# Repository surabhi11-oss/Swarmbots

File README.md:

# Swarmbots - Autonomous Robotic Swarm Platform

Autonomous multi-robot swarm platform featuring distributed mesh coordination, differential-drive motion control, an onboard OLED graphical interface, and a zero-install real-time Web Digital Twin.

---

## Repository Structure

```
Swarmbots/
├── firmware/
│   ├── main/                          # Core autonomous robot firmware & motor drivers
│   │   ├── SwarmBot/                  # Main ESP32 sketch for full swarm operations
│   │   └── README.md
│   ├── oled/                          # Unified OLED Display & Web Subsystem
│   │   ├── SwarmBot_OLED/             # Standalone production ESP32 OLED firmware
│   │   │   ├── SwarmBot_OLED.ino      # Main sketch entry point & cooperative scheduler
│   │   │   ├── config.h               # Global compile-time defaults & pin mappings
│   │   │   └── src/
│   │   │       ├── config/            # Non-Volatile Storage (NVS) & pin validation
│   │   │       ├── controllers/       # Motor safety & autonomous pause hooks
│   │   │       ├── display/           # U8g2 abstraction & runtime I2C scanner
│   │   │       ├── input/             # Single-button multi-gesture state machine
│   │   │       ├── state/             # Centralized robot telemetry & UI state model
│   │   │       ├── ui/                # UI rendering, boot animation & XBM assets
│   │   │       └── web/               # SoftAP Web server, live digital twin & API
│   │   ├── swarmbot_simulator.html    # Standalone browser testing & interaction harness
│   │   └── README.md                  # Comprehensive OLED subsystem documentation
│   ├── display/                       # Display drivers and documentation
│   └── tests/                         # Hardware diagnostic scripts & sensor tests
└── README.md                          # Repository master documentation
```

---

## OLED & Human-Machine Interface (HMI) Subsystem

The OLED subsystem located at [`firmware/oled/SwarmBot_OLED/`](firmware/oled/SwarmBot_OLED/) provides an interactive interface for configuring, monitoring, and debugging swarm robots without requiring a physical serial connection.

### 1. Key Features
- **Official "Hexa Swarm + S" Logo Boot Animation**:
  - Procedural 7-stage boot sequence rendering 6 swarm nodes, hexagon edges, a 3-pixel thick stylized "S" mark, and a typewriter reveal of `SWARM BOT`.
- **Single-Button Multi-Gesture Finite State Machine**:
  - Designed for minimal hardware complexity using a single tactile switch on `GPIO 27`:
    - **Single Tap (< 450 ms)**: Cycle forward / Next option.
    - **Double Tap (< 350 ms)**: Back / Exit submenu.
    - **Select Hold (1.2 s – 2.8 s)**: Confirm / Enter selected utility.
    - **Power Hold (≥ 3.0 s on Home)**: Emergency Power Halt / Confirmation screen.
- **Smartwatch-Style Carousel Menu**:
  - Smooth 5-item horizontal carousel featuring monochrome XBM icons: `MODES`, `SETTINGS`, `CREDITS`, `POWER`, and `RETURN`.
- **Comprehensive Screen Hierarchy**:
  - `Boot Screen`: Procedural logo reveal and initialization.
  - `Home Screen`: Bot ID, live battery %, dynamic battery icon, textual peer connectivity (`4/4 CONNECTED`), and operational mode chip.
  - `Mode Select`: `Follow Leader` and `Manual Control`.
  - `Sub-Utilities`: Leader tracking distance, speed overrides, and manual drive telemetry.
  - `Settings`: Live I2C address, driver selection, GPIO mappings, and SoftAP IP.
  - `Credits`: Rolling department and team credits (`ECS DEPT - VESIT`).
  - `Power Confirmation & Safe Shutdown`: Hardware latch power-down sequence.
- **Safety Lock (Autonomous Motion Pause)**:
  - While navigating the menu system, autonomous motor actuation is paused automatically to prevent physical collision while handling the robot.

---

## Web Remote & Live 128×64 Digital Twin

The ESP32 broadcasts a self-hosted Wi-Fi Access Point (`SSID: SwarmBot-01`, default IP `192.168.4.1`):

- **Bi-Directional Digital Twin**: Renders a 1:1 pixel-perfect 128×64 HTML5 Canvas representation of the OLED display in real-time.
- **Tactile Button Simulation**:
  - Includes a real-time **60 FPS live hold timer** (`⏱️ 1450 ms`).
  - Smooth dynamic progress bar filling from 0 ms to 3000 ms.
  - Dynamic visual feedback: glowing emerald green ring at 1.5s (Select), pulsing crimson red ring at 3s (Power).
- **Quick Test Shortcuts**: Instant 1-click test chips for `Tap`, `Double-Tap`, `Hold 1.5s`, and `Hold 3s`.
- **Runtime I2C Bus Scanner**: Scan connected I2C peripherals directly from the web browser.
- **NVS Settings Editor**: Change Bot ID, pin assignments, and display driver without recompiling.

---

## Default Pin Mapping

| Peripheral | Signal | ESP32 GPIO | Description |
|---|---|---|---|
| **OLED Display** | SDA | `GPIO 21` | I2C Data Line (SH1106 / SSD1306) |
| **OLED Display** | SCL | `GPIO 22` | I2C Clock Line (400 kHz Fast Mode) |
| **Tactile Button** | SW | `GPIO 27` | Active-LOW pushbutton with internal pull-up |
| **Battery ADC** | V_BAT | `GPIO 34` | ADC1 analog input (resistor divider) |
| **Left Motor** | PWM / DIR | `GPIO 18 / 19` | Differential drive left channel |
| **Right Motor** | PWM / DIR | `GPIO 23 / 5` | Differential drive right channel |
| **Power Latch** | EN | `GPIO -1` (Opt) | Optional auto-power-off latch |

> **Safe Recovery Mode:** If an invalid GPIO configuration is saved to NVS, hold `GPIO 27` down for 5 seconds during power-up to restore all factory defaults.

---

## Quick Start & Flashing Guide

### Prerequisites
- [Arduino IDE 2.x](https://www.arduino.cc/en/software) or [arduino-cli](https://arduino.github.io/arduino-cli/)
- ESP32 Board Package: `esp32 by Espressif Systems` (v2.0.x or v3.0.x)
- Library: `U8g2 by olikraus` (Install via Arduino Library Manager)

### Upload via Arduino IDE
1. Open [`firmware/oled/SwarmBot_OLED/SwarmBot_OLED.ino`](firmware/oled/SwarmBot_OLED/SwarmBot_OLED.ino).
2. Under **Tools > Board**, select **ESP32 Dev Module**.
3. Under **Tools > Port**, select your active COM port.
4. Click **Upload**.
5. Connect your phone or laptop to Wi-Fi `SwarmBot-01` and navigate to `http://192.168.4.1/`.

### Upload via Command Line (`arduino-cli`)
```bash
# Compile firmware
arduino-cli compile --fqbn esp32:esp32:esp32 firmware/oled/SwarmBot_OLED

# Upload to ESP32 (replace COM_PORT with your port, e.g. COM3 or /dev/ttyUSB0)
arduino-cli upload -p COM_PORT --fqbn esp32:esp32:esp32 firmware/oled/SwarmBot_OLED
```

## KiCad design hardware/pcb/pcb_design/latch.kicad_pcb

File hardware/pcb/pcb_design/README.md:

# PCB Design

Store PCB layout, board design, and fabrication files here.

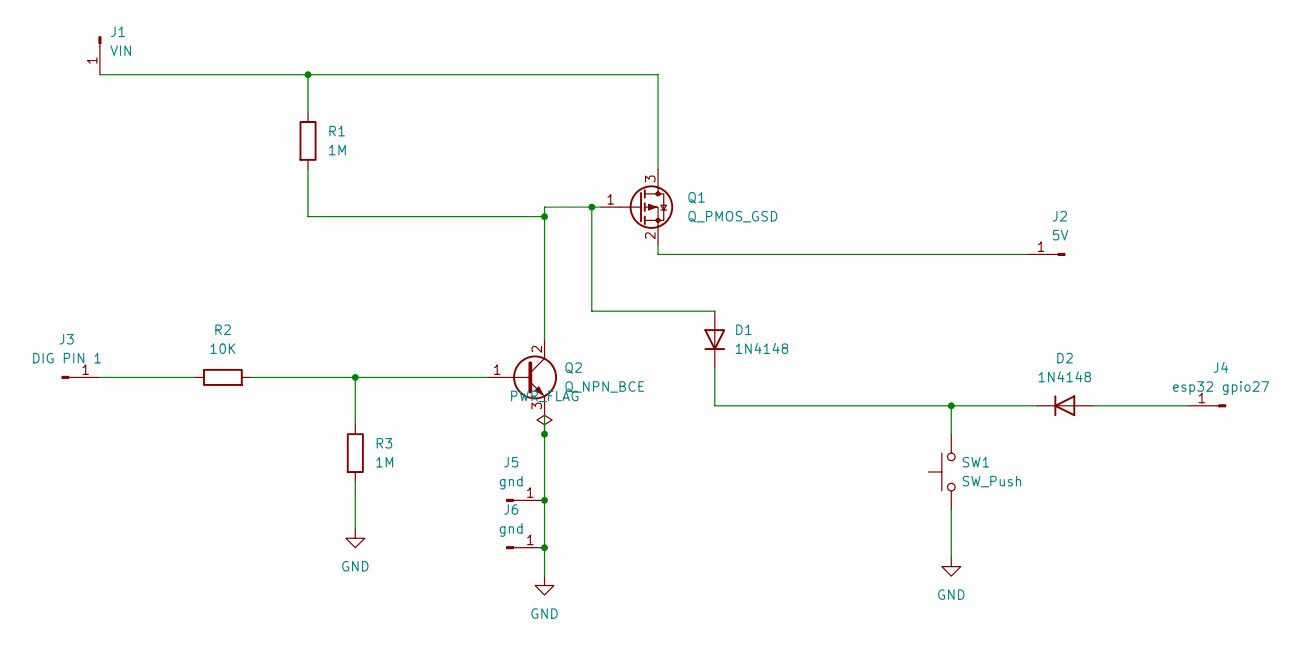
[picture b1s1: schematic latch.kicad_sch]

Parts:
D1, D2: 1N4148; D_DO-35_SOD27_P7.62mm_Horizontal
J1: VIN; PinHeader_1x01_P2.54mm_Vertical
J2: 5V; PinHeader_1x01_P2.54mm_Vertical
J3: DIG PIN 1; PinHeader_1x01_P2.54mm_Vertical
J4: esp32 gpio27; PinHeader_1x01_P2.54mm_Vertical
J5, J6: gnd; PinHeader_1x01_P2.54mm_Vertical
Q1: Q_PMOS_GSD; TO-220-3_Vertical
Q2: Q_NPN_BCE; TRANS_BC547C
R1, R3: 1M; R_Axial_DIN0207_L6.3mm_D2.5mm_P15.24mm_Horizontal
R2: 10K; R_Axial_DIN0207_L6.3mm_D2.5mm_P15.24mm_Horizontal
SW1: SW_Push; SW_PUSH_6mm

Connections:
GND: J5.1, J6.1, Q2.3 (E), R3.2, SW1.1
unnamed: D1.2 (A), Q1.1 (G), Q2.2 (C), R1.2
unnamed: D1.1 (K), D2.1 (K), SW1.2
unnamed: D2.2 (A), J4.1
unnamed: J1.1, Q1.3 (D), R1.1
unnamed: J2.1, Q1.2 (S)
unnamed: J3.1, R2.1
unnamed: Q2.1 (B), R2.2, R3.1

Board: 2 copper layers, 14 parts (0 on the bottom side), 8 nets, no tracks yet.
